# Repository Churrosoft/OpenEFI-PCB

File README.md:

# OpenEFI-PCB
Coleccion de PCB y planos recomendados para montar una OpenEFI

### Sobre el proyecto
OpenEFI es un ECU/EFI programable basada en arduino, totalmente OpenSource, fue creada originalmente para reemplazar una ecu existente en un motor naftero, pero tambien se puede usar para agregar inyeccion y/o encendido electronico a un motor antiguo, cuenta tambien con soporte para DTC's y autodiagnostico
* [OpenEFI](https://github.com/FDSoftware/OpenEFI) [Repo principal con todo el codigo]
* [OpenEFI-Tuner](https://github.com/FDSoftware/OpenEFI-Tuner) [Utilidad para revisar el estado de la ecu y modificarla]
* 
### Placas soportadas
* STM32F407xxxx: uEFI (v2/v3)
* STM32F103c8t6: OpenEFI (v0.5/v1/v2)

### coautores externos:
Dibujos:
Lucacik / ig: https://www.instagram.com/luca.cik/

si quieres usar otra placa basada en Arduino (Uno, Mega,DUE,etc), puedes hacerlo, pero los pcb no te serviran y capaz tengas que modificar ligeramente el codigo y el mapeo de los pines, proximamente agregare mas pcb ademas de mejorar los existentes

This source is distributed WITHOUT ANY EXPRESS OR IMPLIED WARRANTY, INCLUDING OF MERCHANTABILITY, SATISFACTORY QUALITY AND FITNESS FOR A PARTICULAR PURPOSE.

Please see LICENSE file for applicable conditions.

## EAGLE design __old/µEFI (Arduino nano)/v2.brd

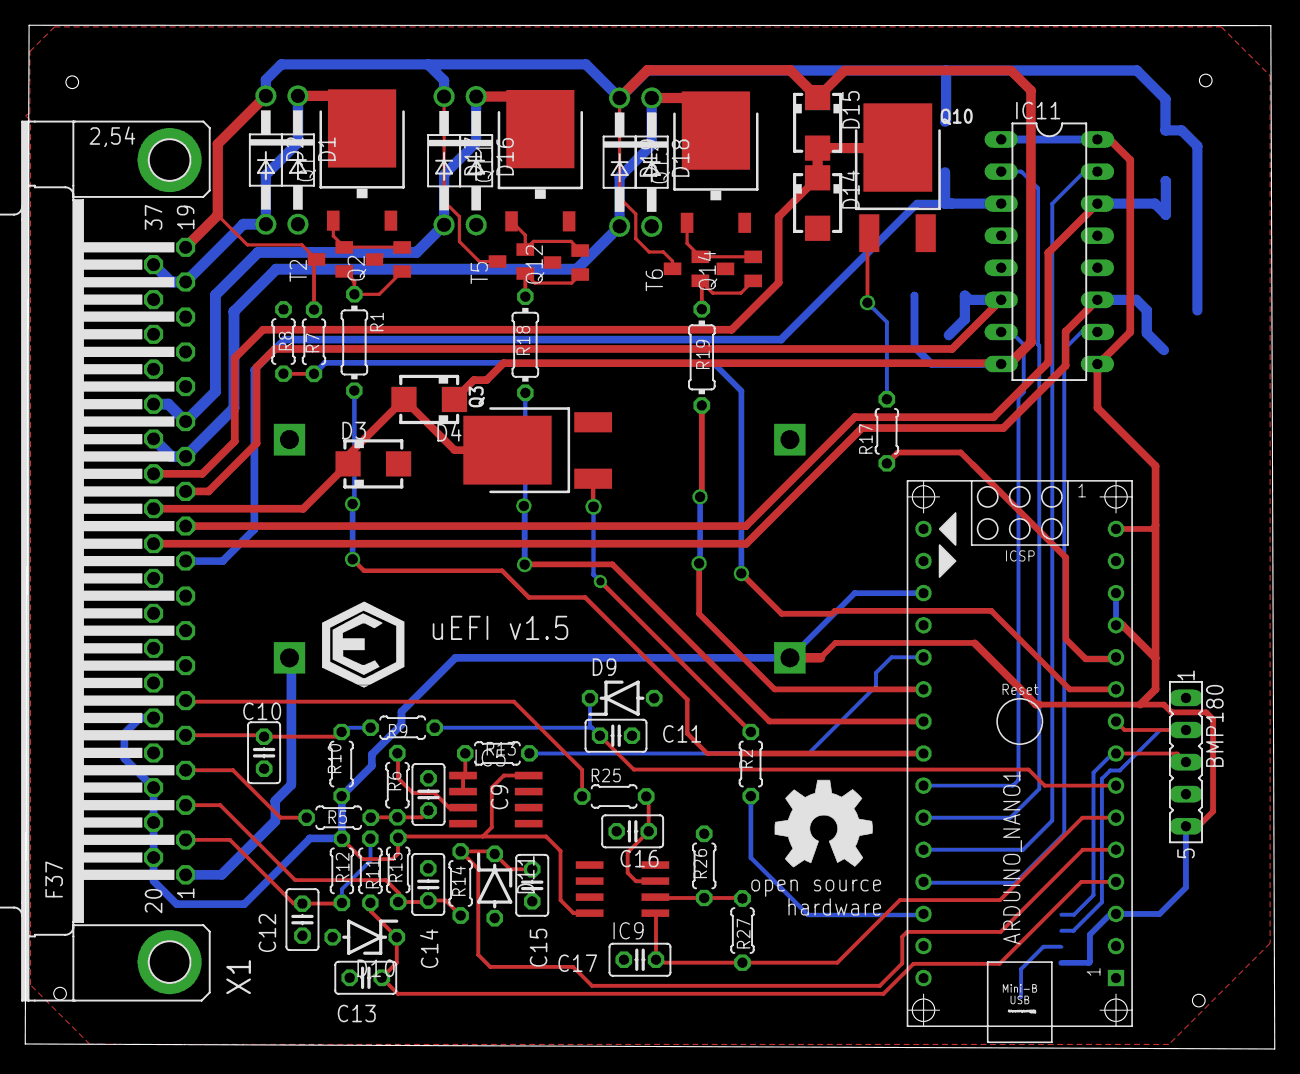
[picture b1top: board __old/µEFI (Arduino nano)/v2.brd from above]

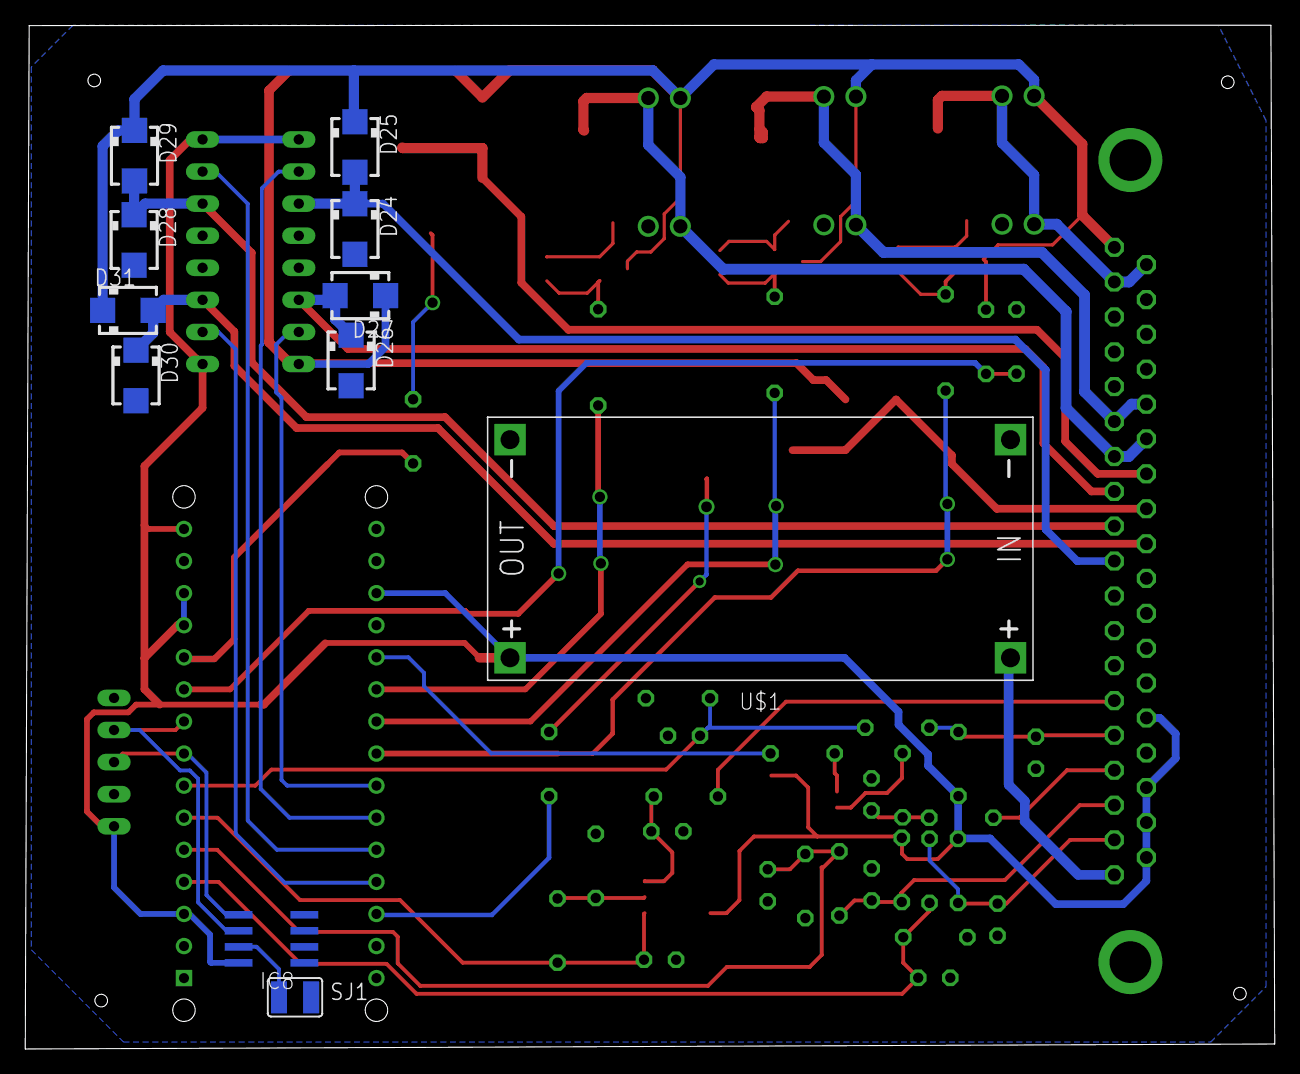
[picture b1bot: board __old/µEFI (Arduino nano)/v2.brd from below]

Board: 2 copper layers, 98.9 x 81.1 mm, 71 parts (11 on the bottom side), 49 nets.

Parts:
ARDUINO_NANO1: ARDUINO_NANO
BMP180: FE05-1
C9, C11: C025-025X050
C10: 0.001uF; C025-025X050
C12, C14, C16: 0.001uf; C025-025X050
C13, C15: 0.1uf; C025-025X050
C17: 0.22uf; C025-025X050
D1, D2, D16, D17, D18, D19: 1N4004; DO41-10
D3, D4, D14, D15, D24, D25, D26, D27, D28, D29, D30, D31: S1M; SMA
D9, D10, D11: 5.1v; ZDIO-5
GOLD_ORB_SM1: OSHWLOGOLOGO8MM; OSHW_8MM
IC5, IC9: LM358D; SO08
IC8: 24AA08SN; SO-08
IC11: L293D; DIL16
Q1, Q11, Q13: Aod442; TO252
Q2, Q12, Q14: BC858ASMD; SOT23-BEC
Q3, Q10: MJD122; DPAK
R1, R18, R19: 0204/7
R2, R17, R26: 1k; 0204/5
R5, R25: 2k; 0204/5
R6, R13, R27: 1.5k; 0204/5
R7: 15k; 0204/5
R8: 5k; 0204/5
R9, R10: 0204/5
R11, R14: 2.2k; 0204/5
R12, R15: 3k; 0204/5
SJ1: SJW
T2, T5, T6: BC848; SOT23
U$1: DC-DC-STEP-DOWN-LM2596
U$2: LOGO
X1: F37HP

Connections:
5V: ARDUINO_NANO1.3, ARDUINO_NANO1.12, ARDUINO_NANO1.13, ARDUINO_NANO1.15, ARDUINO_NANO1.18, BMP180.5, IC5.8, IC8.8, IC9.8, IC11.1, IC11.9, IC11.16, R10.1, R12.2, R15.2, U$1.OUT+, X1.20, X1.21, X1.22, X1.24
ACC: D2.C, D4.C, D15.C, D17.C, D19.C, D25.C, D27.C, D29.C, D31.C, IC11.8, R7.2, T2.3, T5.3, T6.3, X1.19
ACC2: U$1.IN+, X1.1
AIRIN: C10.1, R9.2, R10.2, X1.5
AIROUT: ARDUINO_NANO1.7, C11.1, D9.C, R9.1
CKPIN: R5.1, X1.4
CKPOUT: ARDUINO_NANO1.20, R13.2
CPKOUT: IC5.1, IC5.2, R13.1
ECN1: D16.C, D17.A, Q11.2, X1.14, X1.33
ECN1L: ARDUINO_NANO1.22, R18.2
ECN2: D18.C, D19.A, Q13.2, X1.13, X1.32
ECN2L: ARDUINO_NANO1.21, R19.2
GND: ARDUINO_NANO1.14, ARDUINO_NANO1.19, BMP180.4, C9.2, C10.2, C11.2, C12.2, C13.2, C14.2, C15.2, C16.2, C17.2, D1.A, D3.A, D9.A, D10.A, D11.A, D14.A, D16.A, D18.A, D24.A, D26.A, D28.A, D30.A, IC5.4, IC8.1, IC8.2, IC8.3, IC8.4, IC9.4, IC11.4, IC11.5, IC11.12, IC11.13, Q1.3, Q2.C, Q3.3, Q10.3, Q11.3, Q12.C, Q13.3, Q14.C, R8.1, R26.2, SJ1.2, U$1.IN-, U$1.OUT-, X1.23, X1.25
IAC_A: D24.C, D25.A, IC11.3, X1.10
IAC_B: D26.C, D27.A, IC11.6, X1.12
IAC_C: D28.C, D29.A, IC11.14, X1.11
IAC_D: D30.C, D31.A, IC11.11, X1.29
IAC_LA: ARDUINO_NANO1.25, IC11.2
IAC_LB: ARDUINO_NANO1.24, IC11.7
IAC_LC: ARDUINO_NANO1.26, IC11.15
IAC_LD: ARDUINO_NANO1.27, IC11.10
INY1: D1.C, D2.A, Q1.2, X1.18, X1.37
INYL1A: ARDUINO_NANO1.23, R1.2
LAMB0: R25.1, X1.6
LAMB0OUT: ARDUINO_NANO1.6, C17.1, IC9.1, R27.2
unnamed: Q3.1, R2.2
unnamed: Q1.1, Q2.E, T2.2
unnamed: Q2.B, R1.1, T2.1
unnamed: IC5.3, R6.2
unnamed: C9.1, R5.2, R6.1
unnamed: Q10.1, R17.2
unnamed: Q11.1, Q12.E, T5.2
unnamed: Q12.B, R18.1, T5.1
unnamed: Q13.1, Q14.E, T6.2
unnamed: Q14.B, R19.1, T6.1
unnamed: C16.1, IC9.3, R25.2
unnamed: IC9.2, R26.1, R27.1
unnamed: IC8.7, SJ1.1
RL1: ARDUINO_NANO1.28, R2.1
RL1IN: D3.C, D4.A, Q3.4, X1.30
RL2: ARDUINO_NANO1.11, R17.1
RL2IN: D14.C, D15.A, Q10.4, X1.31
SCL: ARDUINO_NANO1.9, BMP180.2, IC8.6
SDA: ARDUINO_NANO1.8, BMP180.3, IC8.5
TEMPIN: C14.1, R14.1, R15.1, X1.3
TEMPOUT: ARDUINO_NANO1.5, C15.1, D11.C, R14.2
TPSIN: C12.1, R11.1, R12.1, X1.2
TPSOUT: ARDUINO_NANO1.4, C13.1, D10.C, R11.2
VBAT: ARDUINO_NANO1.10, R7.1, R8.2

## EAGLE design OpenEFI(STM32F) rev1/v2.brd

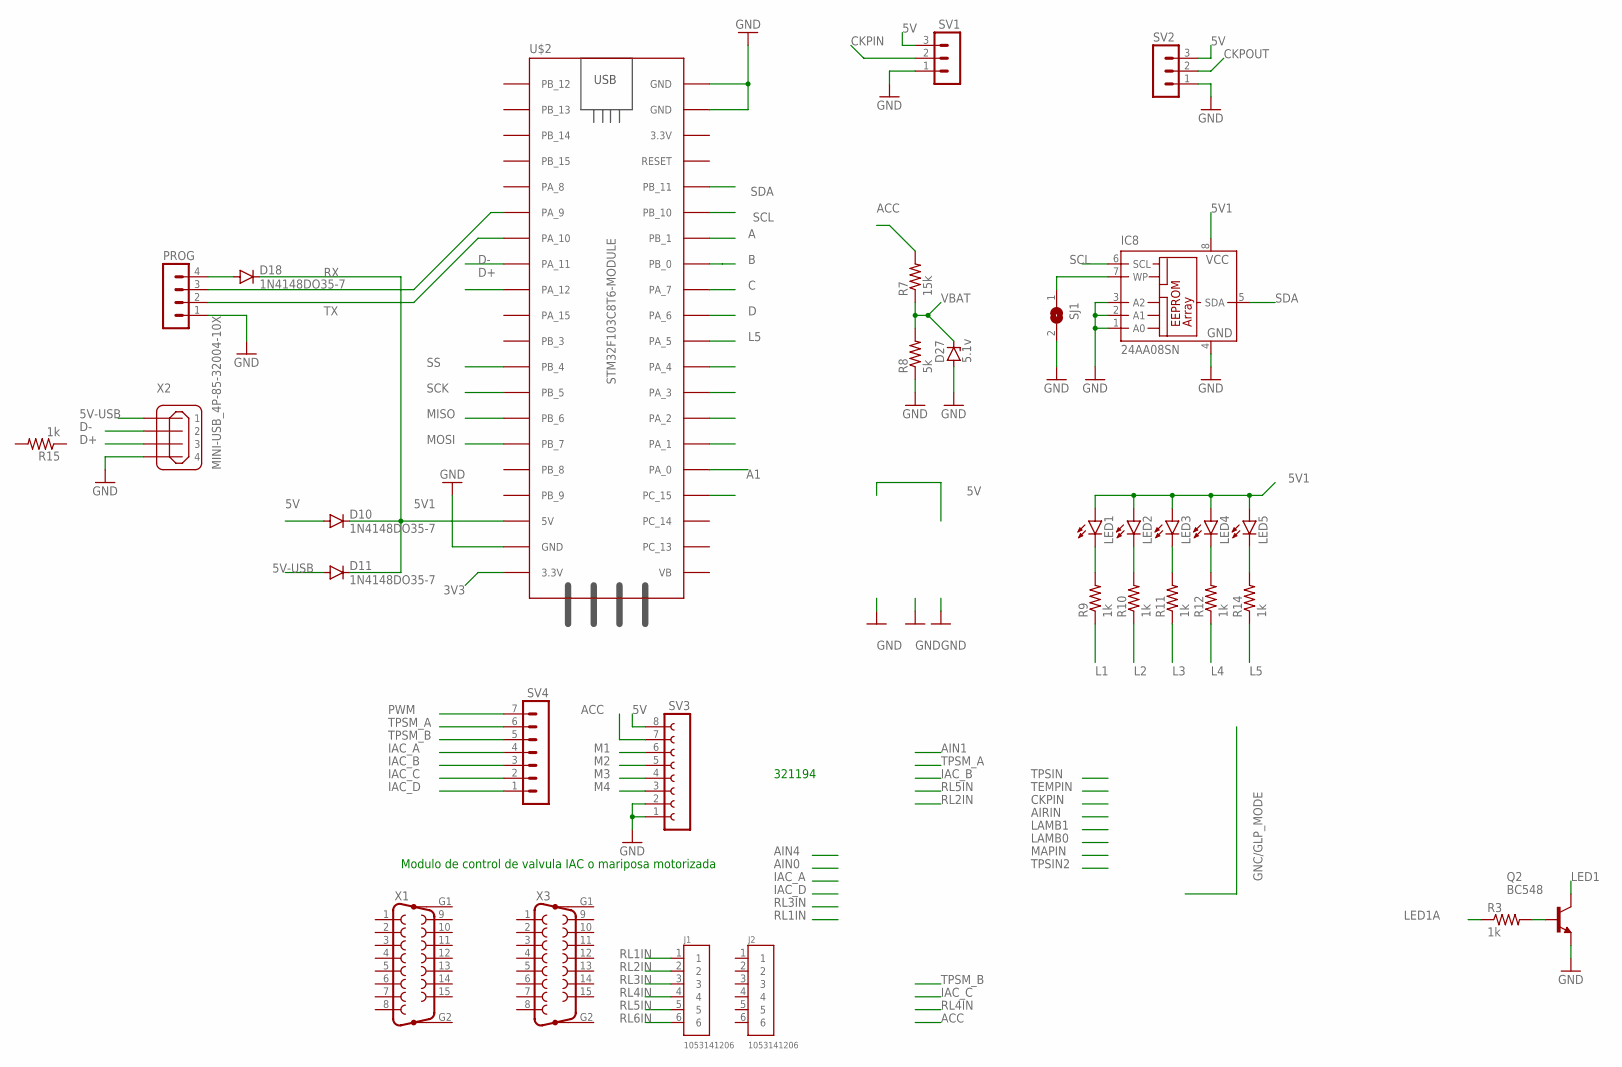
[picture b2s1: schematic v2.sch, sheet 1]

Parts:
D10, D11, D18: 1N4148DO35-7; DO35-7
D27: 5.1v; ZDIO-5
IC8: 24AA08SN; SO-08
J1, J2: 1053141206; MOLEX_1053141206
LED1, LED2, LED3, LED4, LED5: LED3MM
PROG: MA04-1
Q2: BC548; TO92-EBC
R3, R9, R10, R11, R12, R14, R15: 1k; 0204/5
R7: 15k; 0204/5
R8: 5k; 0204/5
SJ1: SJW
SV1, SV2: MA03-1
SV3: FE08-1; FE08
SV4: MA07-1
U$2: STM32F103C8T6-MODULE
X1, X3: F15HP
X2: MINI-USB_4P-85-32004-10X; 85-32004-10X

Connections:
3V3: U$2.3.3V_1 (3.3V); also elsewhere on the board
5V: D10.A, SV1.3, SV2.3, SV3.8; also elsewhere on the board
5V1: D10.C, D11.C, D18.C, IC8.8 (VCC), LED1.A, LED2.A, LED3.A, LED4.A, LED5.A, U$2.5V
5V-USB: D11.A, X2.1
A: U$2.PB_1; also elsewhere on the board
A1: U$2.PA_0; also elsewhere on the board
ACC: R7.2, SV3.7; also elsewhere on the board
B: U$2.PB_0; also elsewhere on the board
C: U$2.PA_7; also elsewhere on the board
CKPIN: SV1.2
CKPOUT: SV2.2
D: U$2.PA_6; also elsewhere on the board
D+: U$2.PA_12, X2.3
D-: U$2.PA_11, X2.2
GND: D27.A, IC8.1 (A0), IC8.2 (A1), IC8.3 (A2), IC8.4 (GND), PROG.1, Q2.E, R8.1, SJ1.2, SV1.1, SV2.1, SV3.1, SV3.2, U$2.GND_1 (GND), U$2.GND_2 (GND), U$2.GND_3 (GND), X2.4; also elsewhere on the board
IAC_A: SV4.4
IAC_B: SV4.3
IAC_C: SV4.2
IAC_D: SV4.1
L1: R9.1
L2: R10.1
L3: R11.1
L4: R12.1
L5: R14.1, U$2.PA_5
LED1: Q2.C
LED1A: R3.1
M1: SV3.6; also elsewhere on the board
M2: SV3.5; also elsewhere on the board
M3: SV3.4; also elsewhere on the board
M4: SV3.3; also elsewhere on the board
MISO: U$2.PB_6
MOSI: U$2.PB_7
unnamed: LED1.K (C), R9.2
unnamed: LED2.K (C), R10.2
unnamed: Q2.B, R3.2
unnamed: LED3.K (C), R11.2
unnamed: LED4.K (C), R12.2
unnamed: LED5.K (C), R14.2
unnamed: IC8.7 (WP), SJ1.1
unnamed: D18.A, PROG.4
PWM: SV4.7
RL1IN: J1.1; also elsewhere on the board
RL2IN: J1.2; also elsewhere on the board
RL3IN: J1.3; also elsewhere on the board
RL4IN: J1.4; also elsewhere on the board
RL5IN: J1.5; also elsewhere on the board
RL6IN: J1.6; also elsewhere on the board
RX: PROG.3, U$2.PA_9
SCK: U$2.PB_5
SCL: IC8.6 (SCL), U$2.PB_10; also elsewhere on the board
SDA: IC8.5 (SDA), U$2.PB_11; also elsewhere on the board
SS: U$2.PB_4
TPSM_A: SV4.6
TPSM_B: SV4.5
TX: PROG.2, U$2.PA_10
VBAT: D27.C, R7.1, R8.2; also elsewhere on the board

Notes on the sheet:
Modulo de control de valvula IAC o mariposa motorizada
321194

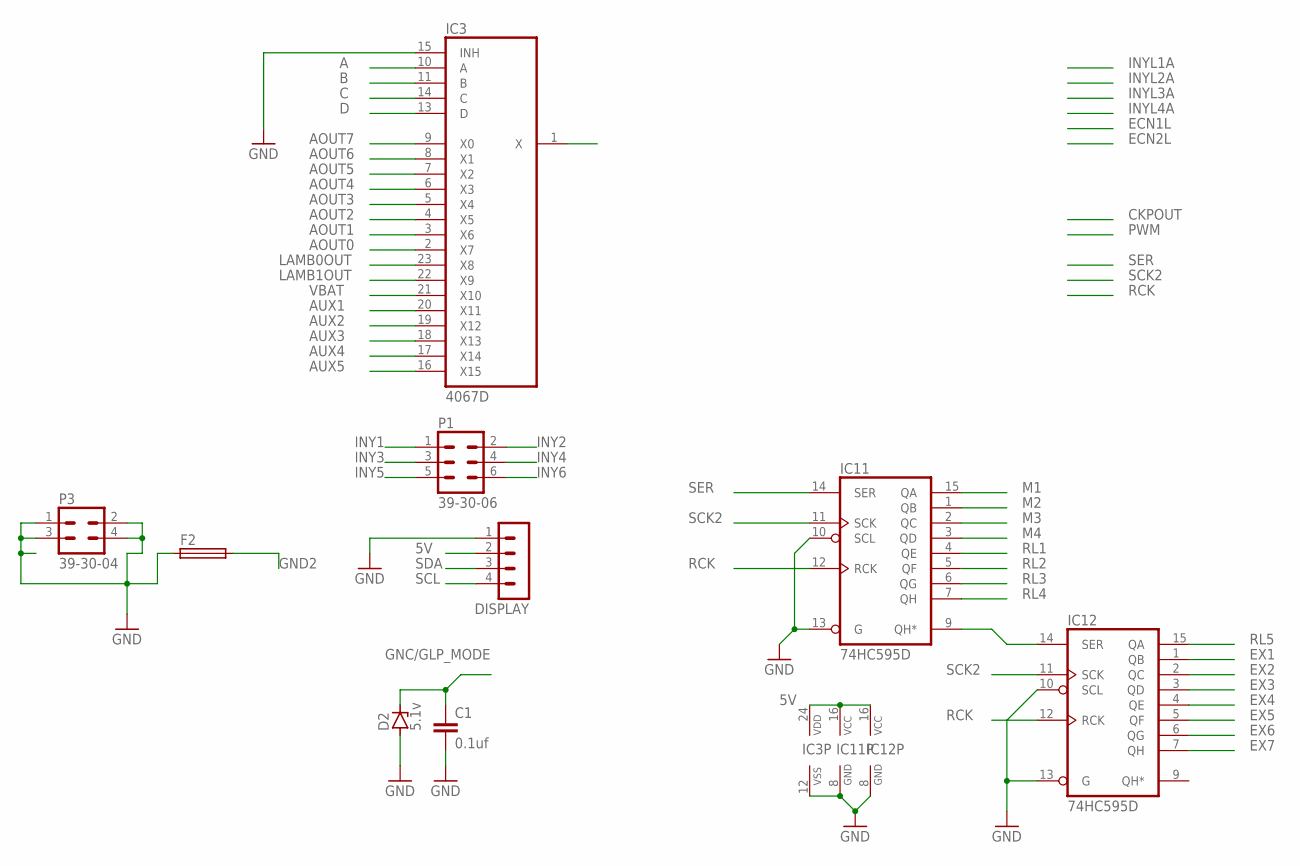
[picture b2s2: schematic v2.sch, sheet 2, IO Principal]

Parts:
C1: 0.1uf; C025-025X050
D2: 5.1v; ZDIO-5
DISPLAY: MA04-1
F2: TE5
IC3: 4067D; SO24W
IC11, IC12: 74HC595D; SO16
P1: 39-30-06; 39-30-?06?
P3: 39-30-04; 39-30-?04?

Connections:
5V: DISPLAY.2, IC3.24 (VDD), IC11.16 (VCC), IC12.16 (VCC); also elsewhere on the board
A: IC3.10 (A); also elsewhere on the board
A0: IC3.1 (X); also elsewhere on the board
AOUT0: IC3.2 (X7); also elsewhere on the board
AOUT1: IC3.3 (X6); also elsewhere on the board
AOUT2: IC3.4 (X5); also elsewhere on the board
AOUT3: IC3.5 (X4); also elsewhere on the board
AOUT4: IC3.6 (X3); also elsewhere on the board
AOUT5: IC3.7 (X2); also elsewhere on the board
AOUT6: IC3.8 (X1); also elsewhere on the board
AOUT7: IC3.9 (X0); also elsewhere on the board
AUX1: IC3.20 (X11)
AUX2: IC3.19 (X12)
AUX3: IC3.18 (X13)
AUX4: IC3.17 (X14)
AUX5: IC3.16 (X15)
B: IC3.11 (B); also elsewhere on the board
C: IC3.14 (C); also elsewhere on the board
D: IC3.13 (D); also elsewhere on the board
EX1: IC12.1 (QB)
EX2: IC12.2 (QC)
EX3: IC12.3 (QD)
EX4: IC12.4 (QE)
EX5: IC12.5 (QF)
EX6: IC12.6 (QG)
EX7: IC12.7 (QH)
GNC/GLP_MODE: C1.1, D2.C
GND: C1.2, D2.A, DISPLAY.1, F2.1, IC3.12 (VSS), IC3.15 (INH), IC11.8 (GND), IC11.10 (SCL), IC11.13 (G), IC12.8 (GND), IC12.10 (SCL), IC12.13 (G), P3.1, P3.2, P3.3, P3.4; also elsewhere on the board
GND2: F2.2; also elsewhere on the board
INY1: P1.1; also elsewhere on the board
INY2: P1.2; also elsewhere on the board
INY3: P1.3; also elsewhere on the board
INY4: P1.4; also elsewhere on the board
INY5: P1.5; also elsewhere on the board
INY6: P1.6; also elsewhere on the board
LAMB0OUT: IC3.23 (X8); also elsewhere on the board
LAMB1OUT: IC3.22 (X9); also elsewhere on the board
M1: IC11.15 (QA); also elsewhere on the board
M2: IC11.1 (QB); also elsewhere on the board
M3: IC11.2 (QC); also elsewhere on the board
M4: IC11.3 (QD); also elsewhere on the board
unnamed: IC11.9 (QH*), IC12.14 (SER)
RCK: IC11.12 (RCK), IC12.12 (RCK)
RL1: IC11.4 (QE); also elsewhere on the board
RL2: IC11.5 (QF); also elsewhere on the board
RL3: IC11.6 (QG); also elsewhere on the board
RL4: IC11.7 (QH); also elsewhere on the board
RL5: IC12.15 (QA); also elsewhere on the board
SCK2: IC11.11 (SCK), IC12.11 (SCK)
SCL: DISPLAY.4; also elsewhere on the board
SDA: DISPLAY.3; also elsewhere on the board
SER: IC11.14 (SER)
VBAT: IC3.21 (X10); also elsewhere on the board

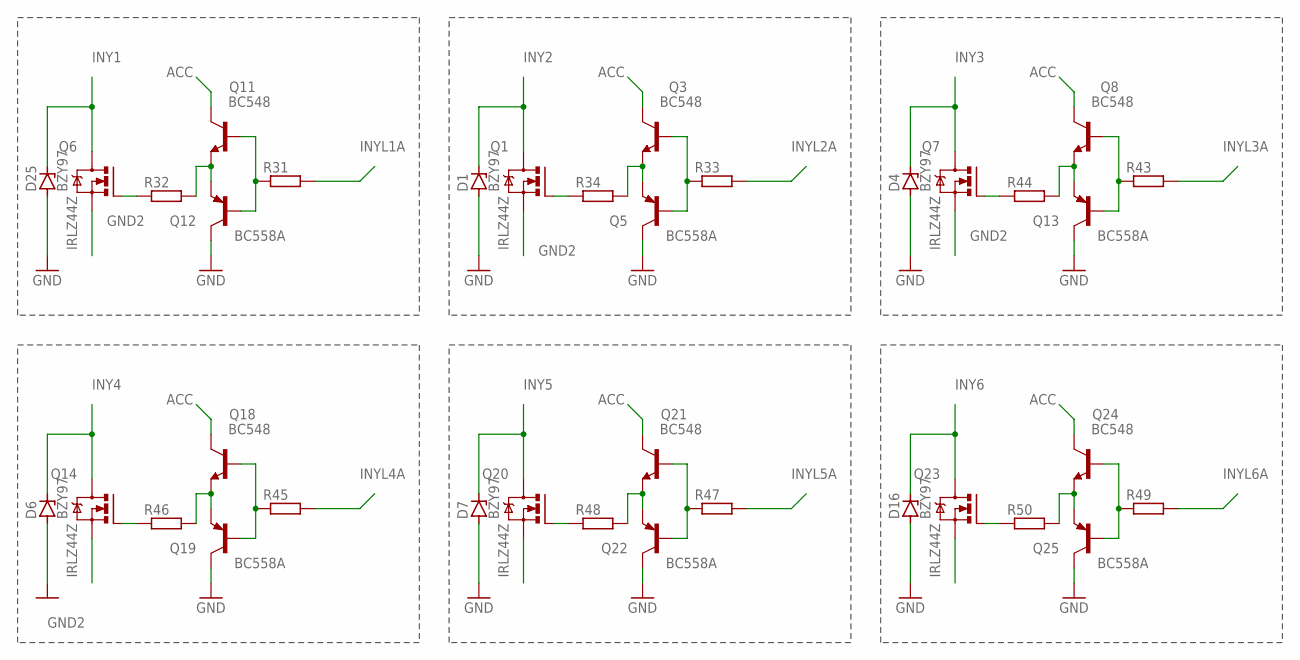
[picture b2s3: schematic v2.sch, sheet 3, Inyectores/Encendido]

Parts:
D1, D4, D6, D7, D16, D25: BZY97; F126Z12
Q1, Q6, Q7, Q14, Q20, Q23: IRLZ44Z; TO220BH
Q3, Q8, Q11, Q18, Q21, Q24: BC548; TO92-EBC
Q5, Q12, Q13, Q19, Q22, Q25: BC558A; TO92-EBC
R31, R32, R33, R34, R43, R44, R45, R46, R47, R48, R49, R50: R-EU_0207/10; 0207/10

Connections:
ACC: Q3.C, Q8.C, Q11.C, Q18.C, Q21.C, Q24.C; also elsewhere on the board
GND: D1.A, D4.A, D6.A, D7.A, D16.A, D25.A, Q5.C, Q12.C, Q13.C, Q19.C, Q22.C, Q25.C; also elsewhere on the board
GND2: Q1.S, Q6.S, Q7.S, Q14.S, Q20.S, Q23.S; also elsewhere on the board
INY1: D25.C, Q6.D; also elsewhere on the board
INY2: D1.C, Q1.D; also elsewhere on the board
INY3: D4.C, Q7.D; also elsewhere on the board
INY4: D6.C, Q14.D; also elsewhere on the board
INY5: D7.C, Q20.D; also elsewhere on the board
INY6: D16.C, Q23.D; also elsewhere on the board
INYL1A: R31.2
INYL2A: R33.2
INYL3A: R43.2
INYL4A: R45.2
INYL5A: R47.2
INYL6A: R49.2
unnamed: Q11.B, Q12.B, R31.1
unnamed: Q11.E, Q12.E, R32.2
unnamed: Q3.B, Q5.B, R33.1
unnamed: Q6.G, R32.1
unnamed: Q3.E, Q5.E, R34.2
unnamed: Q1.G, R34.1
unnamed: Q8.B, Q13.B, R43.1
unnamed: Q8.E, Q13.E, R44.2
unnamed: Q7.G, R44.1
unnamed: Q18.B, Q19.B, R45.1
unnamed: Q18.E, Q19.E, R46.2
unnamed: Q14.G, R46.1
unnamed: Q21.B, Q22.B, R47.1
unnamed: Q21.E, Q22.E, R48.2
unnamed: Q20.G, R48.1
unnamed: Q24.B, Q25.B, R49.1
unnamed: Q24.E, Q25.E, R50.2
unnamed: Q23.G, R50.1

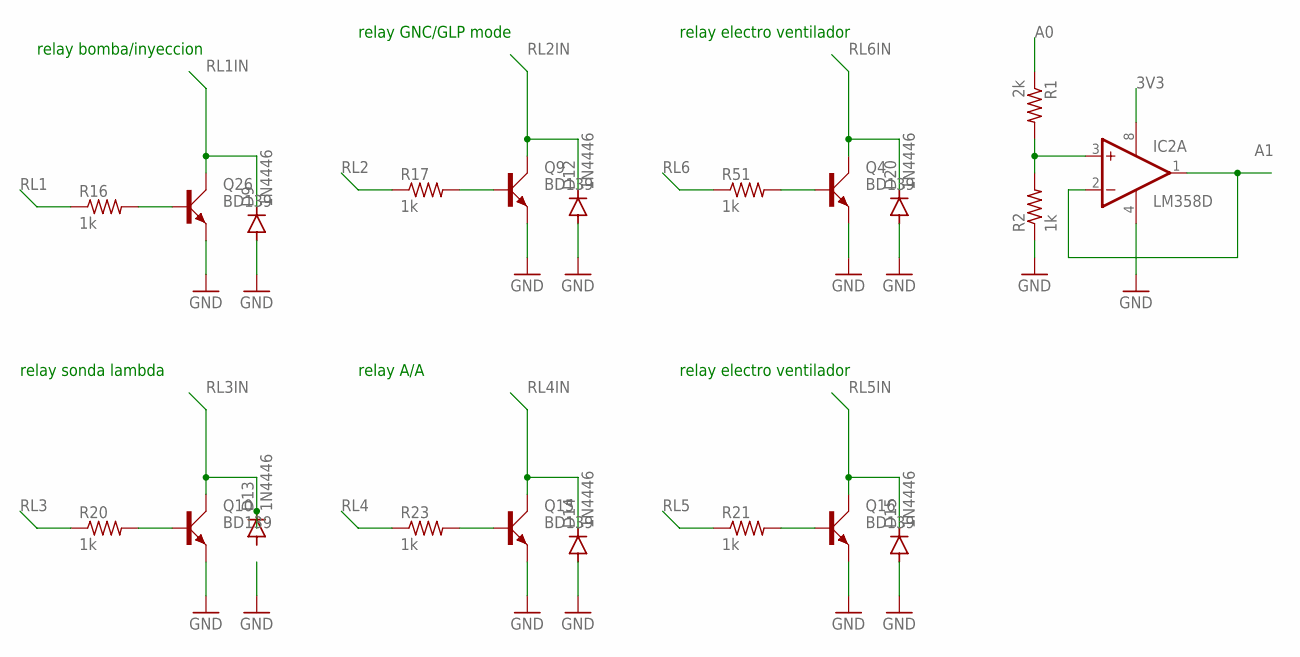
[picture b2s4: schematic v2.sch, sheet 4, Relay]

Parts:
D9, D12, D13, D14, D15, D20: 1N4446; DO35-10
IC2: LM358D; SO08
Q4, Q9, Q10, Q15, Q16, Q26: BD139; TO126AV
R1: 2k; 0204/5
R2, R16, R17, R20, R21, R23, R51: 1k; 0204/5

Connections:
3V3: IC2.8 (V+); also elsewhere on the board
A0: R1.1; also elsewhere on the board
A1: IC2.1 (OUT), IC2.2 (-IN); also elsewhere on the board
GND: D9.A, D12.A, D14.A, D15.A, D20.A, IC2.4 (V-), Q4.E, Q9.E, Q10.E, Q15.E, Q16.E, Q26.E, R2.1; also elsewhere on the board
unnamed: Q26.B, R16.2
unnamed: Q16.B, R21.2
unnamed: Q9.B, R17.2
unnamed: IC2.3 (+IN), R1.2, R2.2
unnamed: Q10.B, R20.2
unnamed: Q15.B, R23.2
unnamed: Q4.B, R51.2
RL1: R16.1; also elsewhere on the board
RL1IN: D9.C, Q26.C; also elsewhere on the board
RL2: R17.1; also elsewhere on the board
RL2IN: D12.C, Q9.C; also elsewhere on the board
RL3: R20.1; also elsewhere on the board
RL3IN: D13.C, Q10.C; also elsewhere on the board
RL4: R23.1; also elsewhere on the board
RL4IN: D14.C, Q15.C; also elsewhere on the board
RL5: R21.1; also elsewhere on the board
RL5IN: D15.C, Q16.C; also elsewhere on the board
RL6: R51.1
RL6IN: D20.C, Q4.C; also elsewhere on the board

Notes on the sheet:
relay bomba/inyeccion
relay GNC/GLP mode
relay sonda lambda
relay A/A
relay electro ventilador

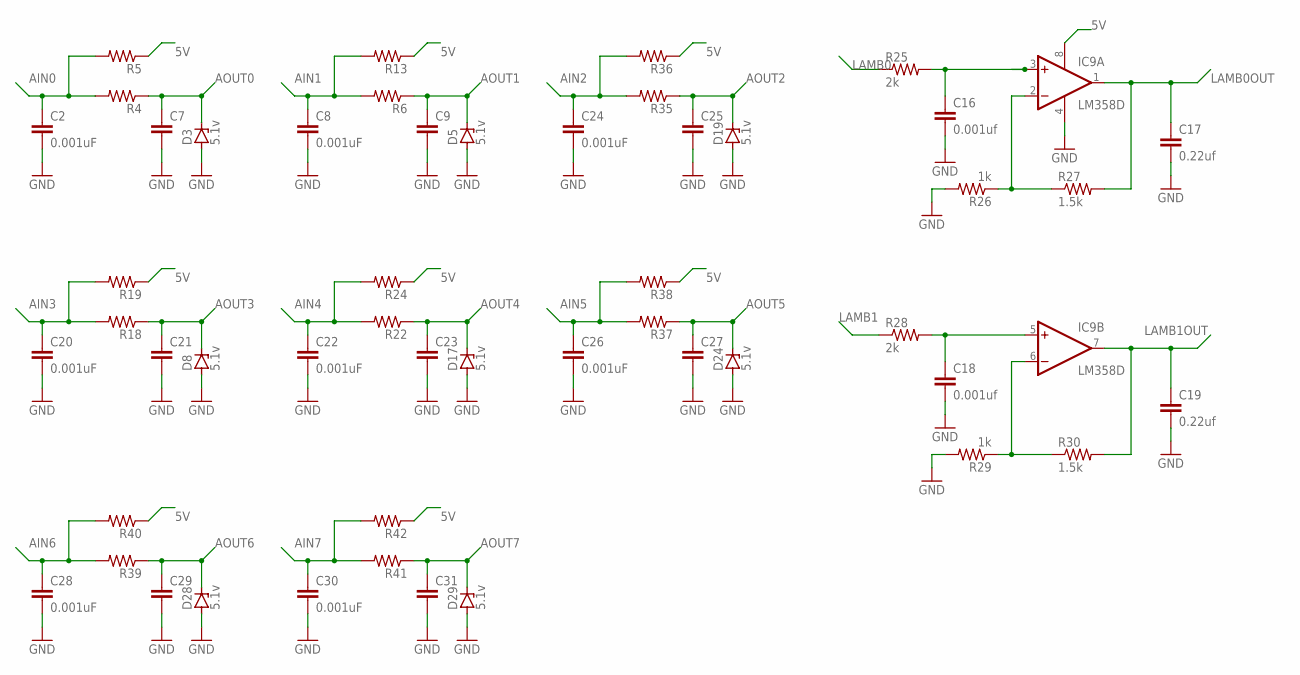
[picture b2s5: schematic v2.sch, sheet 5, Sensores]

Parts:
C2, C8, C20, C22, C24, C26, C28, C30: 0.001uF; C025-025X050
C7, C9, C21, C23, C25, C27, C29, C31: C-EU025-025X050; C025-025X050
C16, C18: 0.001uf; C025-025X050
C17, C19: 0.22uf; C025-025X050
D3, D5, D8, D17, D19, D24, D28, D29: 5.1v; ZDIO-5
IC9: LM358D; SO08
R4, R5, R6, R13, R18, R19, R22, R24, R35, R36, R37, R38, R39, R40, R41, R42: R-US_0204/5; 0204/5
R25, R28: 2k; 0204/5
R26, R29: 1k; 0204/5
R27, R30: 1.5k; 0204/5

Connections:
5V: IC9.8 (V+), R5.1, R13.1, R19.1, R24.1, R36.1, R38.1, R40.1, R42.1; also elsewhere on the board
AIN0: C2.1, R4.2, R5.2
AIN1: C8.1, R6.2, R13.2
AIN2: C24.1, R35.2, R36.2
AIN3: C20.1, R18.2, R19.2
AIN4: C22.1, R22.2, R24.2
AIN5: C26.1, R37.2, R38.2
AIN6: C28.1, R39.2, R40.2
AIN7: C30.1, R41.2, R42.2
AOUT0: C7.1, D3.C, R4.1; also elsewhere on the board
AOUT1: C9.1, D5.C, R6.1; also elsewhere on the board
AOUT2: C25.1, D19.C, R35.1; also elsewhere on the board
AOUT3: C21.1, D8.C, R18.1; also elsewhere on the board
AOUT4: C23.1, D17.C, R22.1; also elsewhere on the board
AOUT5: C27.1, D24.C, R37.1; also elsewhere on the board
AOUT6: C29.1, D28.C, R39.1; also elsewhere on the board
AOUT7: C31.1, D29.C, R41.1; also elsewhere on the board
GND: C2.2, C7.2, C8.2, C9.2, C16.2, C17.2, C18.2, C19.2, C20.2, C21.2, C22.2, C23.2, C24.2, C25.2, C26.2, C27.2, C28.2, C29.2, C30.2, C31.2, D3.A, D5.A, D8.A, D17.A, D19.A, D24.A, D28.A, D29.A, IC9.4 (V-), R26.2, R29.2; also elsewhere on the board
LAMB0: R25.1
LAMB0OUT: C17.1, IC9.1 (OUT), R27.2; also elsewhere on the board
LAMB1: R28.1
LAMB1OUT: C19.1, IC9.7 (OUT), R30.2; also elsewhere on the board
unnamed: C18.1, IC9.5 (+IN), R28.2
unnamed: C16.1, IC9.3 (+IN), R25.2
unnamed: IC9.2 (-IN), R26.1, R27.1
unnamed: IC9.6 (-IN), R29.1, R30.1

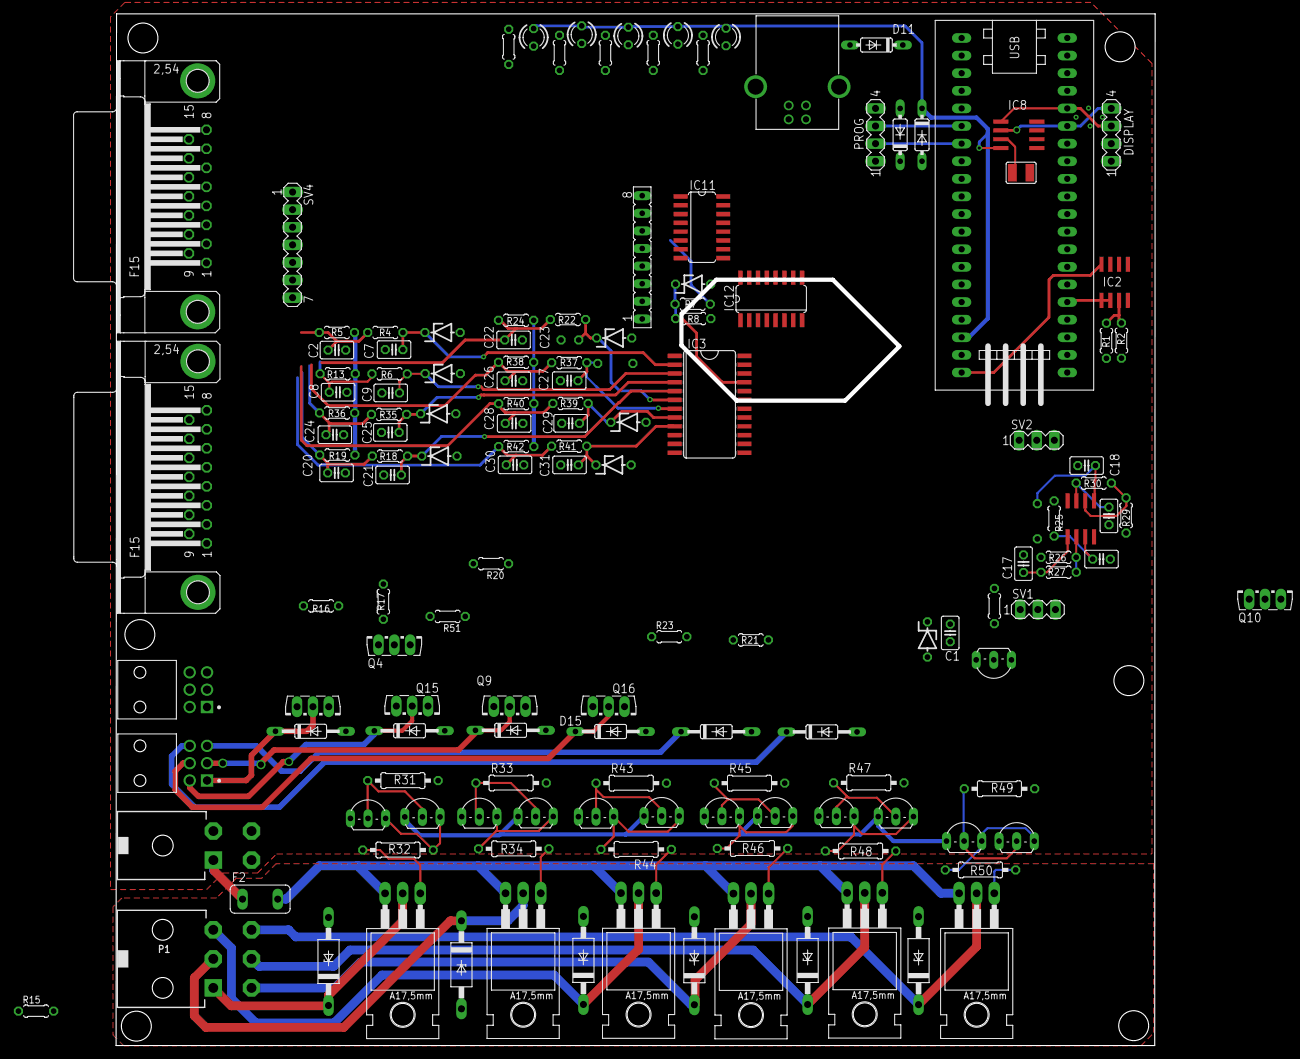
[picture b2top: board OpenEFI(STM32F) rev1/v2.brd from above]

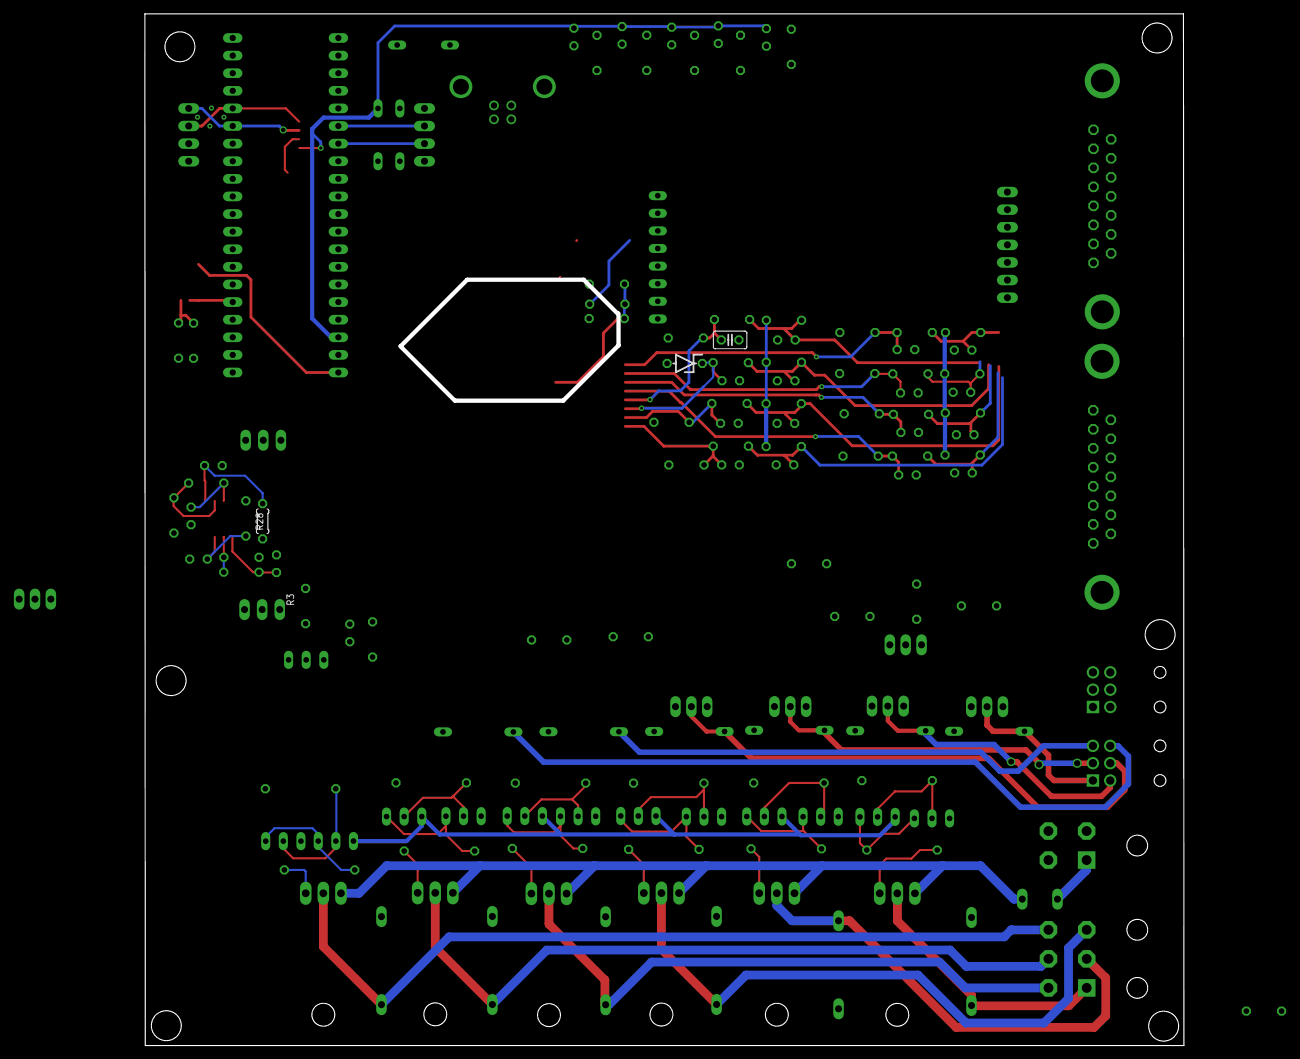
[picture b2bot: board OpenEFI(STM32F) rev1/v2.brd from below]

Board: 2 copper layers, 149.9 x 148.8 mm, 149 parts (3 on the bottom side), 101 nets.

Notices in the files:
parts and their libraries:
con-molex-mini-fit: Copyright (C) 2011, Bob Starr
diy-modules: Released under the Creative Commons Attribution 4.0 International License: http://creativecommons.org/licenses/by/4.0
